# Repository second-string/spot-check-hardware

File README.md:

# spot-check-hardware
Board design and assembly files for the Spot Check project

* Firmware repo: https://github.com/dot4qu/spot-check-firmware
* Backend API repo: https://github.com/dot4qu/spot-check-api
* Configuration iOS app repo: https://github.com/dot4qu/spot-check-ios

More pictures of overall enclosure and project found in the firmware repo.

## Rev 3.1

**Use this version!!**

Fixes the issues in rev 3, mainly:
* Adds the missing capacitor between BTST and SW output of BQ24196 battery charger
* Switches the ESP footprint to the correct ESP32-WROVER footprint (all I/O on sides and longer length, no I/O on bottom like WROOM)
* Add 1uF cap acros ESP32 EN pin to slow its rise time enough to allow DTR/RTS auto-programming circuit to work
* Removed all the now-unneccesary zero ohm resistors

## Rev 3

_See rev. 3.1 PCBA, only minor differences_

Huge rework and addition from rev 2. Adds:
* USB to UART IC for power and programming instead of UART header (still on board for backup use if needed)
* Battery charger IC for supporting battery powered operation instead of wall outlet power
* Integrated e-ink driver circuit using shift register, boost converter to produce +22/-20V, additional regulators to filter to +/-15V, and a small-pitch FPC connector to connect to e-ink display
* Switch to ESP32-WROVER for additional on-module SRAM needed to run `epdiy` open source e-ink firmware

## Rev 2

The main, working revision for properly displaying text on an LED strip ticker with only an ESP32 driving everything. Powered from a 5V 1.5A+ barrel jack.

## Rev 1

The OG. This was an ESP chip that ran the main application logic that then communicated serially over UART to an ATMega328p to display the text on the LED strips (as the LED text libraries are only developed for Arduino). Zero support for this, I don't think I ever got the serial communication working super well since I had no protocol and the ESP would spew nonsense signals on boot. Oh to be young and naive again (just kidding I still am).

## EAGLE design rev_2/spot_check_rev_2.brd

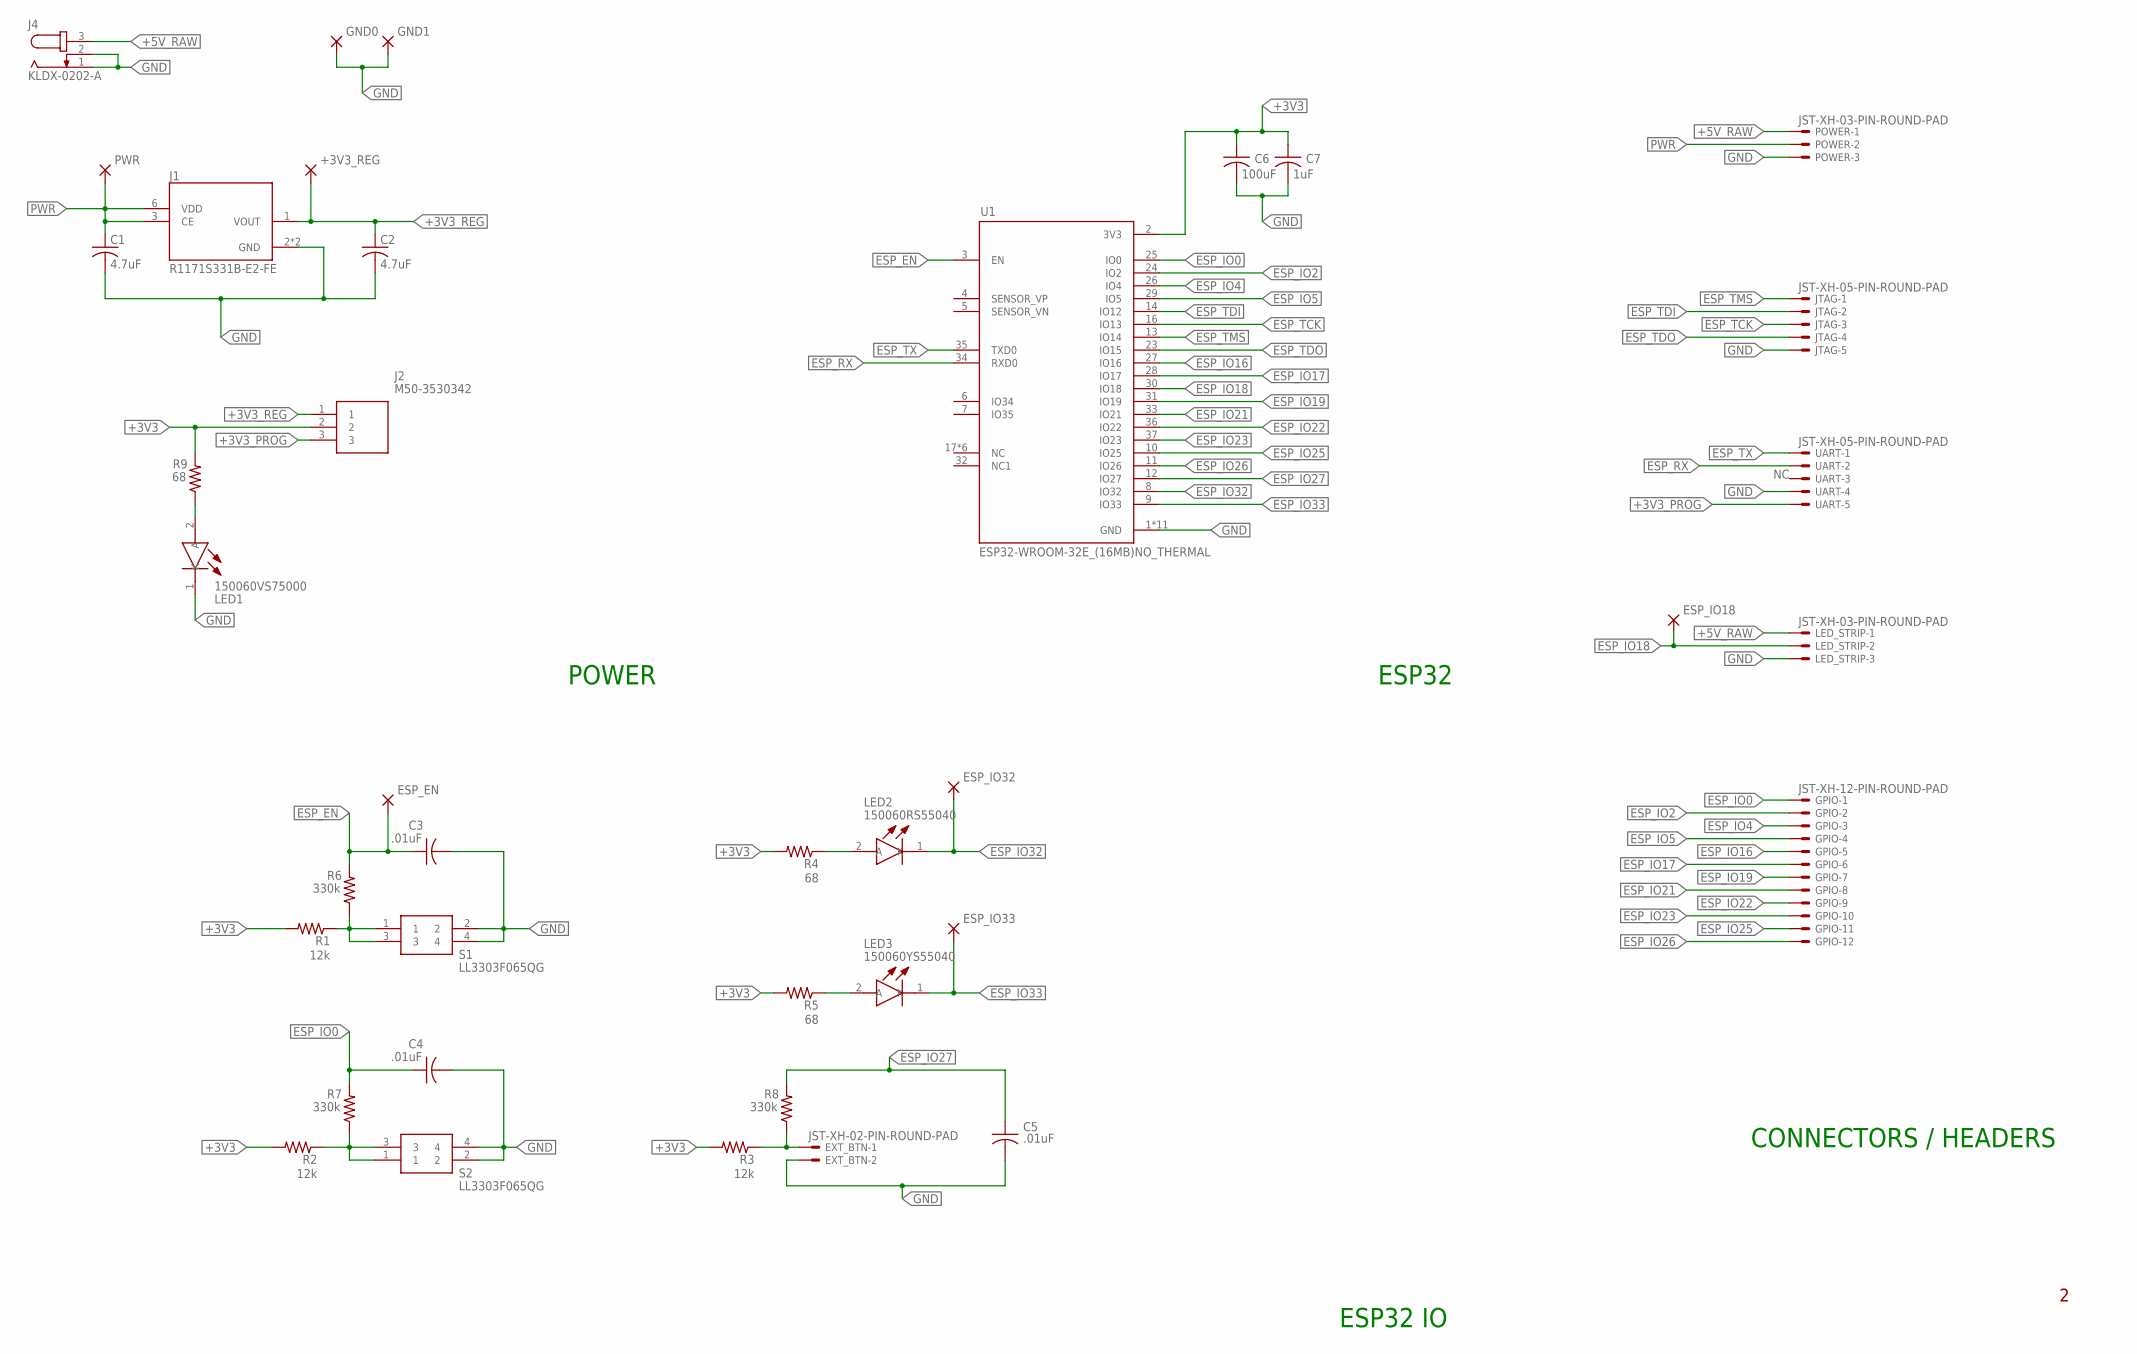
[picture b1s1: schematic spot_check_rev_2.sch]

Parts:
+3V3_REG: TP; 2,54/1,1
C1, C2: 4.7uF; C0805
C3, C4, C5: .01uF; C0805
C6: 100uF; C0805
C7: 1uF; C0805
ESP_EN: TP; 2,54/1,1
ESP_IO18, ESP_IO32, ESP_IO33: TP; 2,54/1,1
EXT_BTN: JST-XH-02-PIN-ROUND-PAD; JST-XH-02-PACKAGE-ROUND-PAD
GND0, GND1: TP; 2,54/1,1
GPIO: JST-XH-12-PIN-ROUND-PAD; JST-XH-12-PACKAGE-ROUND-PAD
J1: R1171S331B-E2-FE; REG_R1171S421B-E2-FE
J2: M50-3530342; HDRV3W40P0X127_1X3_381X210X430
J4: KLDX-0202-A; SPC4077
JTAG: JST-XH-05-PIN-ROUND-PAD; JST-XH-05-PACKAGE-ROUND-PAD
LED1: 150060VS75000; LEDC1608X80N
LED2: 150060RS55040; LEDC1608X80N
LED3: 150060YS55040; LEDC1608X80N
LED_STRIP: JST-XH-03-PIN-ROUND-PAD; JST-XH-03-PACKAGE-ROUND-PAD
POWER: JST-XH-03-PIN-ROUND-PAD; JST-XH-03-PACKAGE-ROUND-PAD
PWR: TP; 2,54/1,1
R1, R2, R3: 12k; R0805
R4, R5, R9: 68; R0805
R6, R7, R8: 330k; R0805
S1, S2: LL3303F065QG
U1: ESP32-WROOM-32E_(16MB)NO_THERMAL; MODULE_ESP32-WROOM-32E_(16MB)
UART: JST-XH-05-PIN-ROUND-PAD; JST-XH-05-PACKAGE-ROUND-PAD

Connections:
+3V3: C6.1, C7.1, J2.2, R1.2, R2.2, R3.2, R4.2, R5.2, R9.2, U1.2 (3V3)
+3V3_PROG: J2.3, UART.5
+3V3_REG: +3V3_REG.1, C2.1, J1.1 (VOUT), J2.1
+5V_RAW: J4.3, LED_STRIP.1, POWER.1
ESP_EN: C3.1, ESP_EN.1, R6.2, U1.3 (EN)
ESP_IO0: C4.1, GPIO.1, R7.2, U1.25 (IO0)
ESP_IO2: GPIO.2, U1.24 (IO2)
ESP_IO4: GPIO.3, U1.26 (IO4)
ESP_IO5: GPIO.4, U1.29 (IO5)
ESP_IO16: GPIO.5, U1.27 (IO16)
ESP_IO17: GPIO.6, U1.28 (IO17)
ESP_IO18: ESP_IO18.1, LED_STRIP.2, U1.30 (IO18)
ESP_IO19: GPIO.7, U1.31 (IO19)
ESP_IO21: GPIO.8, U1.33 (IO21)
ESP_IO22: GPIO.9, U1.36 (IO22)
ESP_IO23: GPIO.10, U1.37 (IO23)
ESP_IO25: GPIO.11, U1.10 (IO25)
ESP_IO26: GPIO.12, U1.11 (IO26)
ESP_IO27: C5.1, R8.2, U1.12 (IO27)
ESP_IO32: ESP_IO32.1, LED2.1 (K), U1.8 (IO32)
ESP_IO33: ESP_IO33.1, LED3.1 (K), U1.9 (IO33)
ESP_RX: U1.34 (RXD0), UART.2
ESP_TCK: JTAG.3, U1.16 (IO13)
ESP_TDI: JTAG.2, U1.14 (IO12)
ESP_TDO: JTAG.4, U1.23 (IO15)
ESP_TMS: JTAG.1, U1.13 (IO14)
ESP_TX: U1.35 (TXD0), UART.1
GND: C1.2, C2.2, C3.2, C4.2, C5.2, C6.2, C7.2, EXT_BTN.2, GND0.1, GND1.1, J1.2 (GND), J1.5 (GND), J4.1, J4.2, JTAG.5, LED1.1 (K), LED_STRIP.3, POWER.3, S1.2, S1.4, S2.2, S2.4, U1.1 (GND), U1.15 (GND), U1.38 (GND), U1.39_1 (GND), U1.39_3 (GND), U1.39_4 (GND), U1.39_6 (GND), U1.39_7 (GND), U1.39_9 (GND), U1.39_13 (GND), U1.39_18 (GND), UART.4
unnamed: EXT_BTN.1, R3.1, R8.1
unnamed: LED2.2 (A), R4.1
unnamed: LED3.2 (A), R5.1
unnamed: LED1.2 (A), R9.1
unnamed: R1.1, R6.1, S1.1, S1.3
unnamed: R2.1, R7.1, S2.1, S2.3
PWR: C1.1, J1.3 (CE), J1.6 (VDD), POWER.2, PWR.1

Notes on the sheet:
POWER
ESP32
ESP32 IO
CONNECTORS / HEADERS

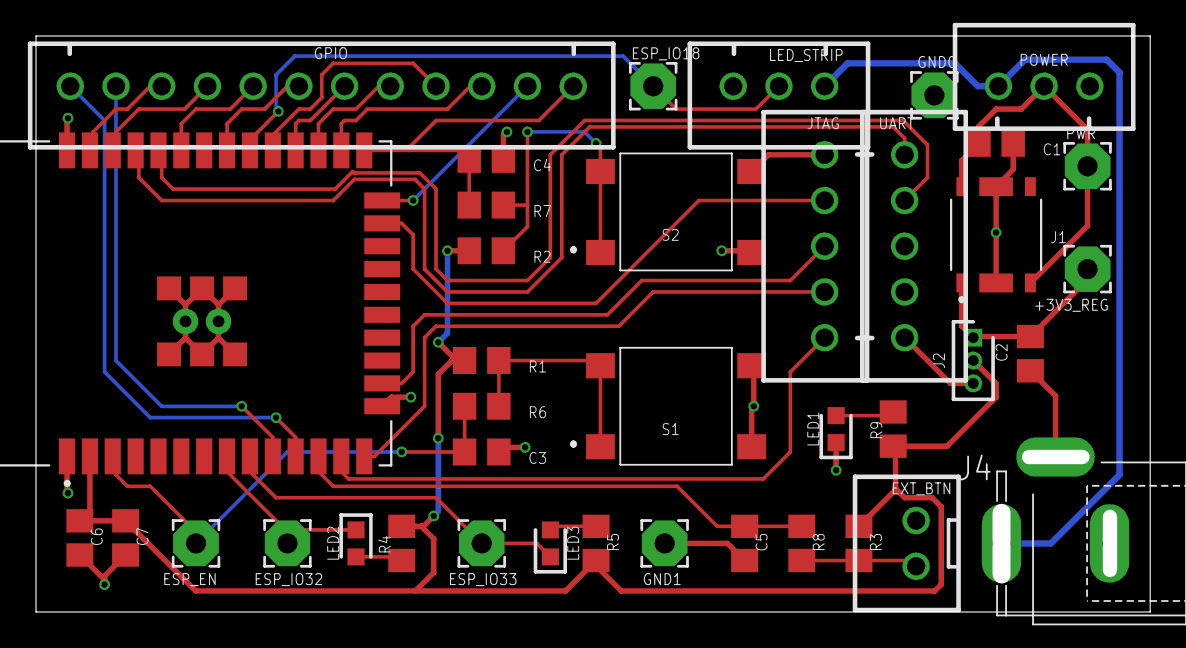
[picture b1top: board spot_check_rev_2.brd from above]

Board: 2 copper layers, 60.9 x 31.0 mm, 39 parts (0 on the bottom side), 35 nets.

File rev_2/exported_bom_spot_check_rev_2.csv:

"Part";"Value";"Device";"Package";"Description";"";
"+3V3_REG";"TP";"2,54/0,8";"2,54/0,8";"THROUGH-HOLE PAD";"";
"C1";"4.7uF";"C-USC0805";"C0805";"CAPACITOR, American symbol";"";
"C2";"4.7uF";"C-USC0805";"C0805";"CAPACITOR, American symbol";"";
"C3";".01uF";"C-USC0805";"C0805";"CAPACITOR, American symbol";"";
"C4";".01uF";"C-USC0805";"C0805";"CAPACITOR, American symbol";"";
"C5";".01uF";"C-USC0805";"C0805";"CAPACITOR, American symbol";"";
"C6";"100uF";"C-USC0805";"C0805";"CAPACITOR, American symbol";"";
"C7";"1uF";"C-USC0805";"C0805";"CAPACITOR, American symbol";"";
"ESP_EN";"TP";"2,54/0,8";"2,54/0,8";"THROUGH-HOLE PAD";"";
"ESP_IO18";"TP";"2,54/0,8";"2,54/0,8";"THROUGH-HOLE PAD";"";
"ESP_IO32";"TP";"2,54/0,8";"2,54/0,8";"THROUGH-HOLE PAD";"";
"ESP_IO33";"TP";"2,54/0,8";"2,54/0,8";"THROUGH-HOLE PAD";"";
"EXT_BTN";"JST-XH-02-PIN-ROUND-PAD";"JST-XH-02-PIN-ROUND-PAD";"JST-XH-02-PACKAGE-ROUND-PAD";"JST XH Connector 2 Pin";"";
"GND0";"TP";"2,54/0,8";"2,54/0,8";"THROUGH-HOLE PAD";"";
"GND1";"TP";"2,54/0,8";"2,54/0,8";"THROUGH-HOLE PAD";"";
"GPIO";"JST-XH-12-PIN-ROUND-PAD";"JST-XH-12-PIN-ROUND-PAD";"JST-XH-12-PACKAGE-ROUND-PAD";"JST XH Connector 2 Pin";"";
"J1";"R1171S331B-E2-FE";"R1171S421B-E2-FE";"REG_R1171S421B-E2-FE";"R1171x SERIES, 2.0A/1.5A LDO REUGULATOR Check prices";"";
"J2";"M50-3530342";"M50-3530342";"HDRV3W40P0X127_1X3_381X210X430";"Headers & Wire Housings 3 WAY SIL VERT PC TAIL P/HDR";"";
"J3";"KLDX-0202-A";"JACK-PLUG1";"SPC4078";"DC POWER JACK";"";
"JTAG";"JST-XH-05-PIN-ROUND-PAD";"JST-XH-05-PIN-ROUND-PAD";"JST-XH-05-PACKAGE-ROUND-PAD";"JST XH Connector 2 Pin";"";
"LED1";"150060VS75000";"150060VS75000";"LEDC1608X80N";"LED,Wurth Elektronik,150060VS75000 Wurth Elektronik 150060VS75000, WL-SMCW Series Green LED, 570 nm, 1608 (0603) Clear, Rectangle Lens SMD Package";"";
"LED2";"150060RS55040";"150060VS75000";"LEDC1608X80N";"LED,Wurth Elektronik,150060VS75000 Wurth Elektronik 150060VS75000, WL-SMCW Series Green LED, 570 nm, 1608 (0603) Clear, Rectangle Lens SMD Package";"";
"LED3";"150060YS55040";"150060VS75000";"LEDC1608X80N";"LED,Wurth Elektronik,150060VS75000 Wurth Elektronik 150060VS75000, WL-SMCW Series Green LED, 570 nm, 1608 (0603) Clear, Rectangle Lens SMD Package";"";
"LED_STRIP";"JST-XH-03-PIN-ROUND-PAD";"JST-XH-03-PIN-ROUND-PAD";"JST-XH-03-PACKAGE-ROUND-PAD";"JST XH Connector 2 Pin";"";
"POWER";"JST-XH-03-PIN-ROUND-PAD";"JST-XH-03-PIN-ROUND-PAD";"JST-XH-03-PACKAGE-ROUND-PAD";"JST XH Connector 2 Pin";"";
"PWR";"TP";"2,54/0,8";"2,54/0,8";"THROUGH-HOLE PAD";"";
"R1";"12k";"R-US_R0805";"R0805";"RESISTOR, American symbol";"";
"R2";"12k";"R-US_R0805";"R0805";"RESISTOR, American symbol";"";
"R3";"12k";"R-US_R0805";"R0805";"RESISTOR, American symbol";"";
"R4";"68";"R-US_R0805";"R0805";"RESISTOR, American symbol";"";
"R5";"68";"R-US_R0805";"R0805";"RESISTOR, American symbol";"";
"R6";"330k";"R-US_R0805";"R0805";"RESISTOR, American symbol";"";
"R7";"330k";"R-US_R0805";"R0805";"RESISTOR, American symbol";"";
"R8";"330k";"R-US_R0805";"R0805";"RESISTOR, American symbol";"";
"R9";"68";"R-US_R0805";"R0805";"RESISTOR, American symbol";"";
"S1";"LL3303F065QG";"LL3303F065QG";"LL3303F065QG";"Pushbutton Switches 50mA 12VDC F065 7.0mm Gull Wing";"";
"S2";"LL3303F065QG";"LL3303F065QG";"LL3303F065QG";"Pushbutton Switches 50mA 12VDC F065 7.0mm Gull Wing";"";
"U1";"ESP32-WROOM-32E_(16MB)NO_THERMAL";"ESP32-WROOM-32E_(16MB)NO_THERMAL";"MODULE_ESP32-WROOM-32E_(16MB)";"Bluetooth, WiFi 802.11b/g/n, Bluetooth v4.2 +EDR, Class 1, 2 and 3 Transceiver Module 2.4GHz ~ 2.5GHz Integrated, Trace Surface Mount  Check prices";"";
"UART";"JST-XH-05-PIN-ROUND-PAD";"JST-XH-05-PIN-ROUND-PAD";"JST-XH-05-PACKAGE-ROUND-PAD";"JST XH Connector 2 Pin";"";

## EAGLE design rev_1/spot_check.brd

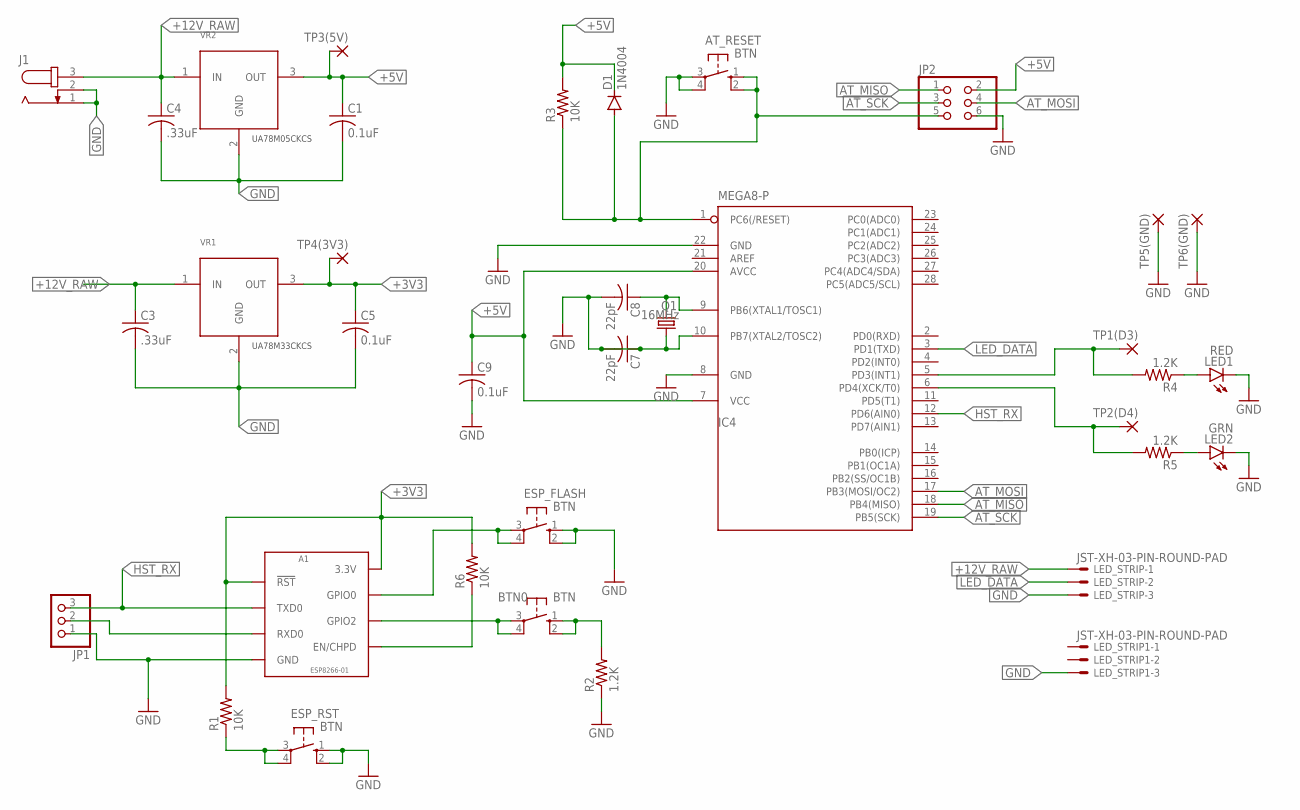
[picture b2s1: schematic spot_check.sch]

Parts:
A1: ESP8266-01; ESP8266_ESP-01_NO-SILKSCREEN
AT_RESET: BTN; B3F-10XX
BTN0: BTN; B3F-10XX
C1, C5, C9: 0.1uF; C050-024X044
C3, C4: .33uF; C050-024X044
C7, C8: 22pF; C050-024X044
D1: 1N4004; DO41-10
ESP_FLASH: BTN; B3F-10XX
ESP_RST: BTN; B3F-10XX
IC4: MEGA8-P; DIL28-3
J1: JACK-PLUG1; SPC4078
JP1: PINHD-1X3/90; 1X03/90
JP2: PINHD-2X3; 2X03
LED1: RED; LED5MM
LED2: GRN; LED5MM
LED_STRIP, LED_STRIP1: JST-XH-03-PIN-ROUND-PAD; JST-XH-03-PACKAGE-ROUND-PAD
Q1: 16MHz; HC49/S
R1, R3, R6: 10K; 0207/10
R2, R4, R5: 1.2K; 0207/10
TP1(D3), TP2(D4), TP3(5V), TP4(3V3), TP5(GND), TP6(GND): 2,54/0,8
VR1: UA78M33CKCS; TO-220-3
VR2: UA78M05CKCS; TO-220-3

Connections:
+3V3: A1.3V3 (3.3V), A1.RST (!RST!), C5.1, R1.2, R6.2, TP4(3V3).1, VR1.3 (OUT)
+5V: C1.1, C9.1, D1.C, IC4.7 (VCC), IC4.20 (AVCC), JP2.2, R3.2, TP3(5V).1, VR2.3 (OUT)
+12V_RAW: C3.1, C4.1, J1.3, LED_STRIP.1, VR1.1 (IN), VR2.1 (IN)
AT_MISO: IC4.18 (PB4(MISO)), JP2.1
AT_MOSI: IC4.17 (PB3(MOSI/OC2)), JP2.4
AT_SCK: IC4.19 (PB5(SCK)), JP2.3
GND: A1.GND, AT_RESET.3, AT_RESET.4 (P1), C1.2, C3.2, C4.2, C5.2, C7.1, C7.2, C8.2, C9.2, ESP_FLASH.1 (S), ESP_FLASH.2 (S1), ESP_RST.1 (S), ESP_RST.2 (S1), IC4.8 (GND), IC4.10 (PB7(XTAL2/TOSC2)), IC4.22 (GND), J1.1, J1.2, JP1.1, JP2.6, LED1.K (C), LED2.K (C), LED_STRIP.3, LED_STRIP1.3, Q1.1, R2.1, TP5(GND).1, TP6(GND).1, VR1.2 (GND), VR2.2 (GND)
HST_RX: A1.TX (TXD0), IC4.12 (PD6(AIN0)), JP1.3
HST_TX: A1.RX (RXD0), JP1.2
LED_DATA: IC4.3 (PD1(TXD)), LED_STRIP.2
unnamed: A1.EN/CH_PD (EN/CHPD), R6.1
unnamed: A1.GPIO2, BTN0.3, BTN0.4 (P1)
unnamed: LED1.A, R4.1
unnamed: BTN0.1 (S), BTN0.2 (S1), R2.2
unnamed: A1.GPIO0, ESP_FLASH.3, ESP_FLASH.4 (P1)
unnamed: LED2.A, R5.1
unnamed: C8.1, IC4.9 (PB6(XTAL1/TOSC1)), Q1.2
unnamed: AT_RESET.1 (S), AT_RESET.2 (S1), D1.A, IC4.1 (PC6(/RESET)), JP2.5, R3.1
unnamed: ESP_RST.3, ESP_RST.4 (P1), R1.1
TP1(D3): IC4.5 (PD3(INT1)), R4.2, TP1(D3).1
TP2(D4): IC4.6 (PD4(XCK/T0)), R5.2, TP2(D4).1

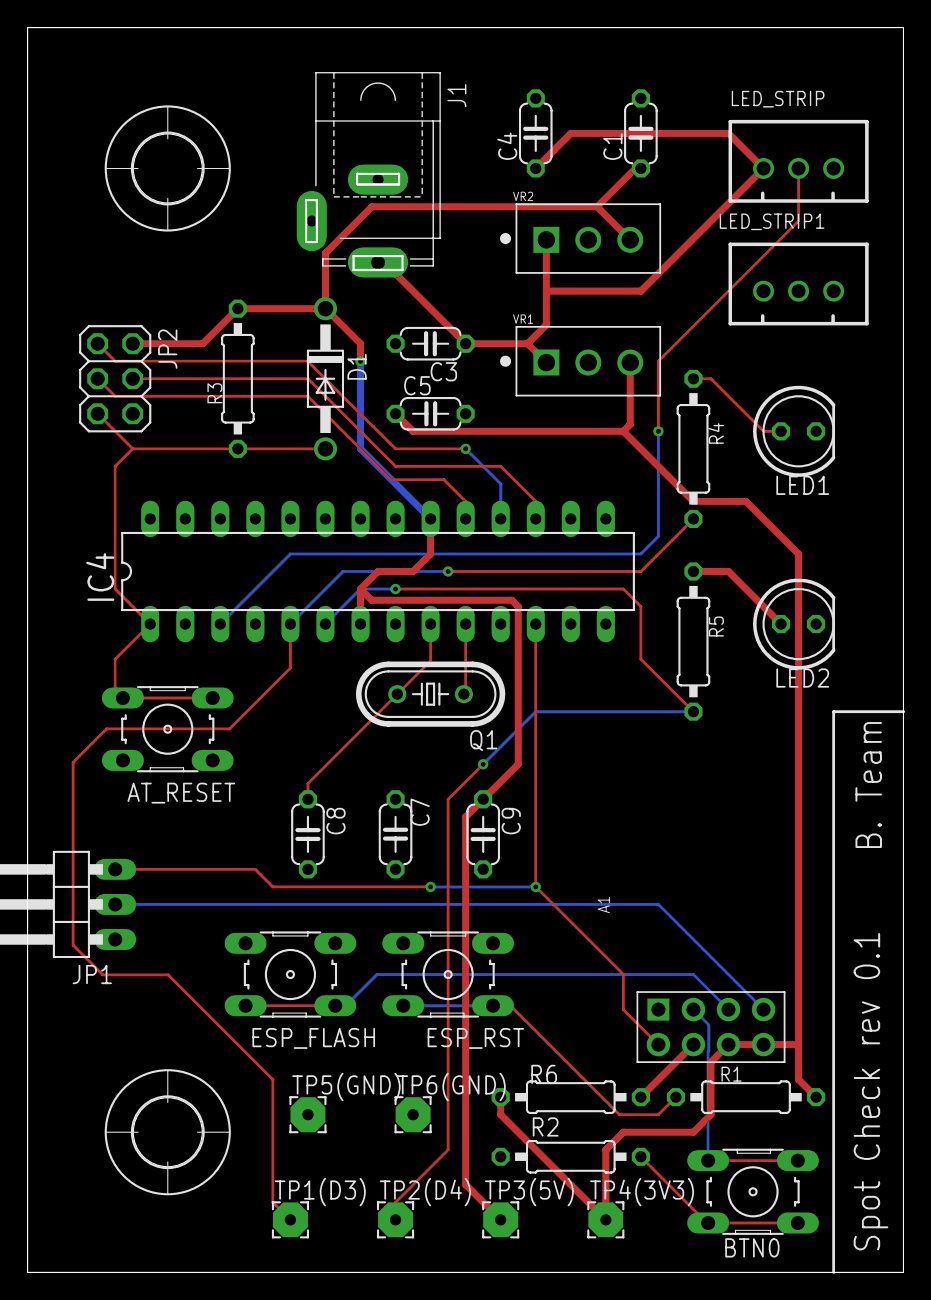
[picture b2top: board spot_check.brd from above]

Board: 2 copper layers, 63.3 x 90.1 mm, 38 parts (0 on the bottom side), 21 nets.

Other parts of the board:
U$1, U$2: 5,0

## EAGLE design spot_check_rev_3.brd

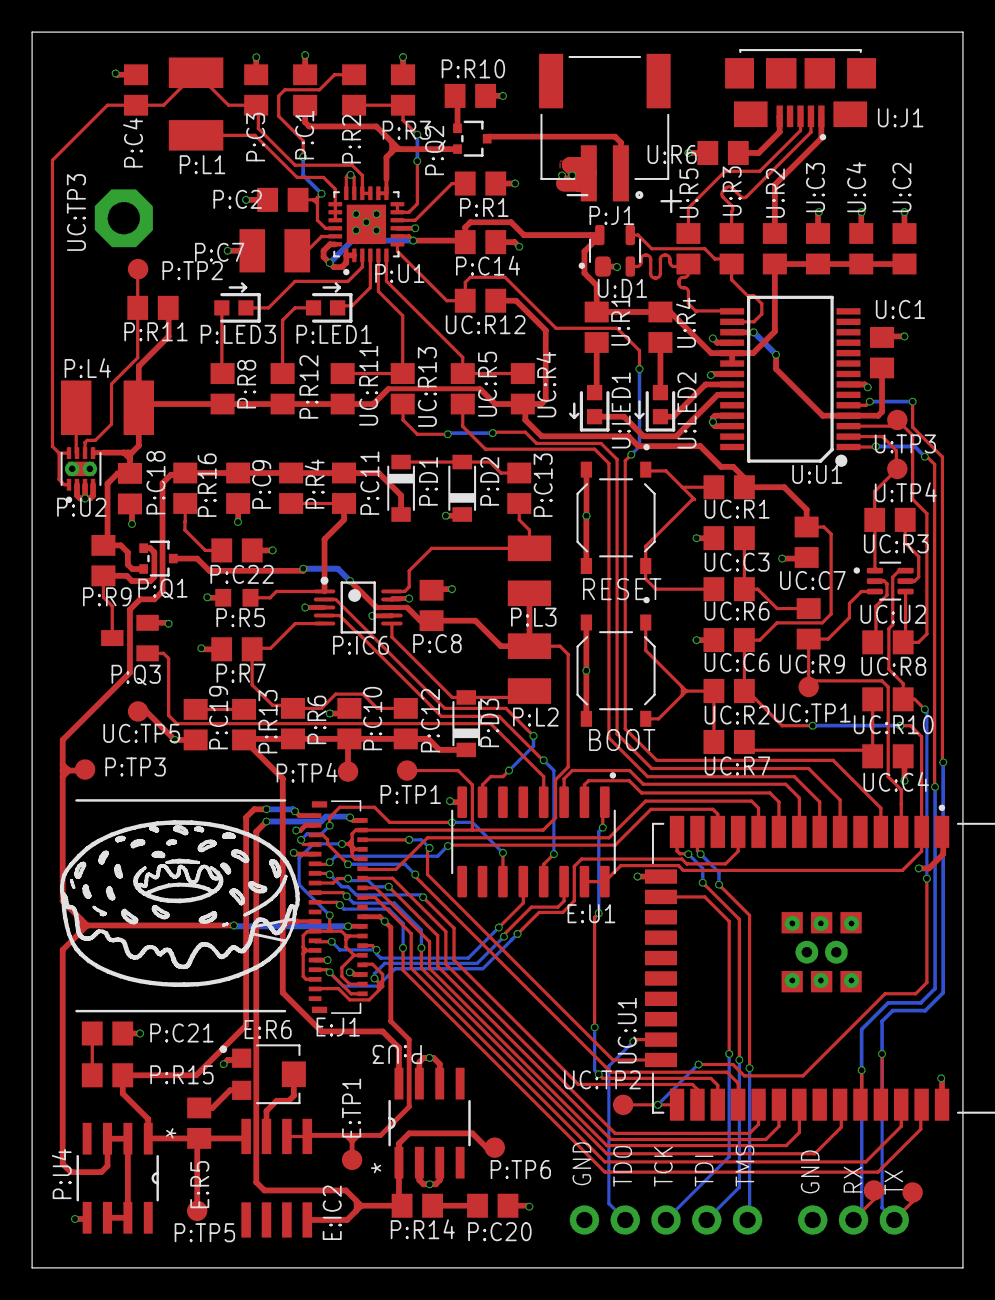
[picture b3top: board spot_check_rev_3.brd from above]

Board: 2 copper layers, 58.0 x 77.0 mm, 109 parts (0 on the bottom side), 89 nets.

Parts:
E:IC2: LM358DR; SO08
E:J1: FH26W-39S-0.3SHW_05_; FH26W39S03SHW05
E:R5: 20k; R0805
E:R6: 10k; TRIM_TC33X-2-333E
E:TP1: TPB1,27; B1,27
E:U1: CD74HC4094M; SOIC127P600X175-16N
P:C1, P:C3, P:C4: 10uF; C0805
P:C2, P:C8: 4.7uF; C0805
P:C7: 6.8uF; C1210
P:C9, P:C10, P:C14: 1uF; C0805
P:C11: 100pF; C0805
P:C12: 4.7pF; C0805
P:C13, P:C20, P:C21: 0.1uF; C0805
P:C18: 22uF; C0805
P:C19, P:C22: 0.33uF; C0805
P:D1, P:D2, P:D3: MBR0520LT1G; SOD3716X135N
P:IC6: LINEAR_TECHNOLOGY_LT1945EMS#PBFLINEAR_TECHNOLOGY_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; LINEAR_TECHNOLOGY_LT1945EMS#PBF_0
P:J1: S2B-PH-SM4-TB(LF)(SN); JST_S2B-PH-SM4-TB(LF)(SN)
P:L1: 2.2uH; L1812
P:L2, P:L3: 22uH; C1210
P:L4: 1uH; L1812
P:LED1: 150060RS55040; LEDC1608X80N
P:LED3: 150060GS55040; LEDC1608X80N
P:Q1, P:Q2: SSM3J132TU,LF; SOT323
P:Q3: MMBT3904,215; SOT23
P:R1: 470; R0805
P:R2, P:R3: 330k; R0805
P:R4: 397k; R0805
P:R5: 27.1k; R0603
P:R6: 1M; R0805
P:R7: 59k; R0805
P:R8, P:R10: 1k; R0805
P:R9: 20k; R0805
P:R11: 178k; R0805
P:R12: 620; R0805
P:R13, P:R14, P:R15, P:R16: 22; R0805
P:TP1, P:TP2, P:TP3, P:TP4, P:TP5, P:TP6: TPB1,27; B1,27
P:U1: BQ24196RGER; QFN50P400X400X100-25N
P:U2: TPS62082DSGR; SON50P200X200X80-9N
P:U3: MC78L15ACDR2G; SOIC127P600X175-8N
P:U4: MC79L15ACDR2G; SOIC127P600X175-8N
U:C1, U:C4: 100nF; C0805
U:C2: 4.7uF; C0805
U:C3: 10nF; C0805
U:D1: DRTR5V0U2SR-7; SOT143
U:J1: 10118192-0002LF; AMPHENOL_10118192-0002LF
U:LED1: 150060YS55040; LEDC1608X80N
U:LED2: 150060BS55040; LEDC1608X80N
U:R1: 270; R0805
U:R2, U:R3, U:R5, U:R6: 0; R0805
U:R4: 330; R0805
U:TP1, U:TP2, U:TP3, U:TP4: TPB1,27; B1,27
U:U1: INTERFACE-FT232RL(SSOP28); SSOP28-0.65-10.2X5.2MM
UC:C3, UC:C4: .01uF; C0805
UC:C6: 22uF; C0805
UC:C7: 1uF; C0805
UC:JTAG: JST-XH-05-PIN-ROUND-PAD; JST-XH-05-PACKAGE-ROUND-PAD
UC:R1, UC:R2: 12k; R0805
UC:R3, UC:R8: 10k; R0805
UC:R4, UC:R11, UC:R12: 4.7k; R0805
UC:R5, UC:R9, UC:R10, UC:R13: 0; R0805
UC:R6, UC:R7: 330k; R0805
UC:S1, UC:S2: PTS526_SM08_SMTR2_LFS; SW_PTS526_SM08_SMTR2_LFS
UC:TP1, UC:TP2, UC:TP5: TPB1,27; B1,27
UC:TP3: TPPAD1-20; P1-20
UC:U1: ESP32-WROOM-32E_(16MB); MODULE_ESP32-WROOM-32E_(16MB)
UC:U2: BC848CDW1T1G; SOT65P210X110-6N
UC:X1: JST-XH-03-PIN-ROUND-PAD; JST-XH-03-PACKAGE-ROUND-PAD

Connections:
3V3_CTRL: E:U1.4, P:Q3.1
3V3_CTRLD: E:J1.4, E:J1.8, E:J1.10, E:J1.25, E:J1.26, E:J1.29, E:J1.30, E:J1.35, E:J1.36, P:C8.1, P:IC6.8, P:L2.1, P:L3.1, P:Q1.3, P:TP1.TP
3V3_REG: E:U1.15, E:U1.16, P:C18.1, P:L4.2, P:Q1.2, P:R8.2, P:R9.2, P:R11.2, P:R12.2, P:U2.5, UC:C6.1, UC:C7.1, UC:R1.2, UC:R2.2, UC:R4.1, UC:R11.1, UC:R12.1, UC:U1.2
5V_USB: P:C14.1, P:U1.1, P:U1.2, P:U1.8, P:U1.24, U:C2.1, U:C3.1, U:C4.1, U:D1.4, U:R1.2, U:R2.2, U:R4.2, U:U1.19, U:U1.20
15V: E:IC2.8, E:J1.2, P:R14.2, P:TP6.TP, P:U3.1
22V: E:J1.23, P:C10.2, P:C12.2, P:D3.C, P:R6.1, P:R13.2, P:TP4.TP, P:U3.8
22V_CTRL: E:U1.13, P:IC6.4
-15V: E:IC2.4, E:J1.1, E:R5.1, P:R15.2, P:TP5.TP, P:U4.1
-20V: E:J1.24, P:C9.1, P:C11.1, P:D1.A, P:R4.2, P:R16.2, P:TP3.TP, P:U4.2, P:U4.3, P:U4.6, P:U4.7
-20V_CTRL: E:U1.7, P:IC6.2
BQ_INT: P:U1.7, UC:R12.2, UC:U1.4
BQ_SCL: P:U1.5, UC:R11.2, UC:R13.1
BQ_SDA: P:U1.6, UC:R4.2, UC:R5.1
DISP_CE: E:J1.6, UC:U1.24
DISP_CLK: E:J1.5, UC:U1.28
DISP_CLKV: E:J1.33, E:J1.38, UC:U1.11
DISP_D0: E:J1.12, UC:U1.10
DISP_D1: E:J1.13, UC:U1.26
DISP_D2: E:J1.14, UC:U1.29
DISP_D3: E:J1.15, UC:U1.30
DISP_D4: E:J1.16, UC:U1.31
DISP_D5: E:J1.17, UC:U1.33
DISP_D6: E:J1.18, UC:U1.36
DISP_D7: E:J1.19, UC:U1.37
DISP_SPH: E:J1.11, UC:U1.12
DTR: U:TP4.TP, U:U1.2, UC:R3.2, UC:U2.1
E:DISP_GMODE: E:J1.27, E:J1.28, E:U1.12
E:DISP_OE: E:J1.7, E:U1.11
E:DISP_SPV: E:J1.32, E:J1.37, E:U1.14
E:DISP_VCOMMON: E:IC2.1, E:IC2.2, E:J1.22, E:TP1.TP
E:N$2: E:R5.2, E:R6.3
E:N$3: E:IC2.3, E:R6.2
ESP_RX: U:TP1.TP, U:U1.1, UC:U1.34, UC:X1.2
ESP_TX: U:TP2.TP, U:U1.5, UC:U1.35, UC:X1.1
GND: E:J1.3, E:J1.9, E:J1.31, E:J1.34, E:R6.1, E:U1.8, P:C1.2, P:C2.2, P:C3.2, P:C4.2, P:C7.2, P:C8.2, P:C9.2, P:C10.1, P:C14.2, P:C18.2, P:C19.2, P:C20.2, P:C21.2, P:C22.2, P:D2.C, P:IC6.3, P:IC6.7, P:IC6.9, P:J1.2, P:Q3.2, P:R1.1, P:R3.1, P:R5.1, P:R7.2, P:R10.1, P:U1.9, P:U1.17, P:U1.18, P:U1.25, P:U2.2, P:U2.3, P:U2.4, P:U2.9, P:U2.9_1, P:U2.9_2, P:U3.2, P:U3.3, P:U3.6, P:U3.7, P:U4.5, U:C1.2, U:C2.2, U:C3.2, U:C4.2, U:D1.1, U:R6.2, U:U1.7, U:U1.18, U:U1.21, U:U1.25, U:U1.26, UC:C3.2, UC:C4.2, UC:C6.2, UC:C7.2, UC:JTAG.5, UC:S1.3, UC:S1.4, UC:S2.3, UC:S2.4, UC:TP3.TP, UC:TP5.TP, UC:U1.1, UC:U1.15, UC:U1.38, UC:X1.3
P:3V3_PG: P:R11.1, P:TP2.TP, P:U2.6
P:BQ_PG: P:LED3.1, P:U1.3
P:BQ_REGN: P:C2.1, P:R2.2, P:U1.22
P:BQ_STAT: P:LED1.1, P:U1.4
P:N$1: P:C1.1, P:Q2.2, P:U1.13, P:U1.14
P:N$2: P:R2.1, P:R3.2, P:U1.11, P:U1.12
P:N$3: P:L1.1, P:U1.19, P:U1.20, P:U1.21
P:N$4: P:J1.1, P:Q2.3
P:N$5: P:C7.1, P:U1.23
P:N$6: P:R1.2, P:U1.10
P:N$7: P:LED3.2, P:R8.1
P:N$8: P:C3.1, P:C4.1, P:L1.2, P:U1.15, P:U1.16, P:U2.1, P:U2.8
P:N$9: P:Q2.1, P:R10.2
P:N$10: P:C12.1, P:IC6.5, P:R6.2, P:R7.1
P:N$11: P:L4.1, P:U2.7
P:N$12: P:LED1.2, P:R12.1
P:N$13: P:D3.A, P:IC6.6, P:L2.2
P:N$14: P:C13.2, P:D1.C, P:D2.A
P:N$15: P:Q1.1, P:Q3.3, P:R9.1
P:N$16: P:C13.1, P:IC6.10, P:L3.2
P:N$17: P:C11.2, P:IC6.1, P:R4.1, P:R5.2
P:N$19: P:C22.1, P:R16.1
P:N$20: P:C21.1, P:R15.1
P:N$21: P:C20.1, P:R14.1
P:N$22: P:C19.1, P:R13.1
RTS: U:TP3.TP, U:U1.3, UC:R8.2, UC:U2.4
SHR_CLK: E:U1.3, UC:U1.8
SHR_DATA: E:U1.2, UC:U1.9
SHR_STR: E:U1.1, UC:U1.27
U:FT232_RX_IND: U:LED2.1, U:U1.22
U:FT232_TX_IND: U:LED1.1, U:U1.23
U:N$1: U:LED1.2, U:R1.1
U:N$2: U:LED2.2, U:R4.1
U:N$3: U:J1.1, U:R2.1
U:N$4: U:C1.1, U:U1.4, U:U1.17
U:N$7: U:J1.5, U:R6.1
U:USBD1_N: U:J1.2, U:R3.1
U:USBD1_P: U:J1.3, U:R5.1
U:USBD2_N: U:D1.3, U:R3.2, U:U1.16
U:USBD2_P: U:D1.2, U:R5.2, U:U1.15
UC:ESP_EN: UC:R9.2, UC:TP1.TP, UC:U1.3, UC:U2.3
UC:ESP_IO0: UC:R10.2, UC:TP2.TP, UC:U1.25, UC:U2.6
UC:ESP_TCK: UC:JTAG.3, UC:U1.16
UC:ESP_TDI: UC:JTAG.2, UC:U1.14
UC:ESP_TDO: UC:JTAG.4, UC:U1.23
UC:ESP_TMS: UC:JTAG.1, UC:U1.13
UC:N$1: UC:R3.1, UC:U2.5
UC:N$2: UC:R13.2, UC:U1.6
UC:N$3: UC:R5.2, UC:U1.7
UC:N$4: UC:R8.1, UC:U2.2
UC:N$5: UC:R1.1, UC:R6.1, UC:S1.1, UC:S1.2
UC:N$6: UC:R2.1, UC:R7.1, UC:S2.1, UC:S2.2
UC:N$7: UC:C4.1, UC:R7.2, UC:R10.1
UC:N$9: UC:C3.1, UC:R6.2, UC:R9.1

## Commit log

2022-04-24 Committing rev 3 files matching rev 3 mfgd PCB
2022-04-24 Add other repo links to readme
2022-04-24 Move to nested dirs for each rev
2022-04-24 Symlinks don't work 🤦🏼
2022-04-24 Add gerber zip along w/ BOM and datasheets
2022-04-24 Add rev_1 and rev_2 files
2022-05-19 Add rev 3 schematic pdfs
2022-05-19 Add all rev 3.1 project files, datasheets, gerbers, and schematics
2022-05-19 Add rev info to readme for what each rev is/does/changes
2022-10-09 Add newest gerber zip for rev 3.1
2022-10-09 Add photos and update readme for board pictures
